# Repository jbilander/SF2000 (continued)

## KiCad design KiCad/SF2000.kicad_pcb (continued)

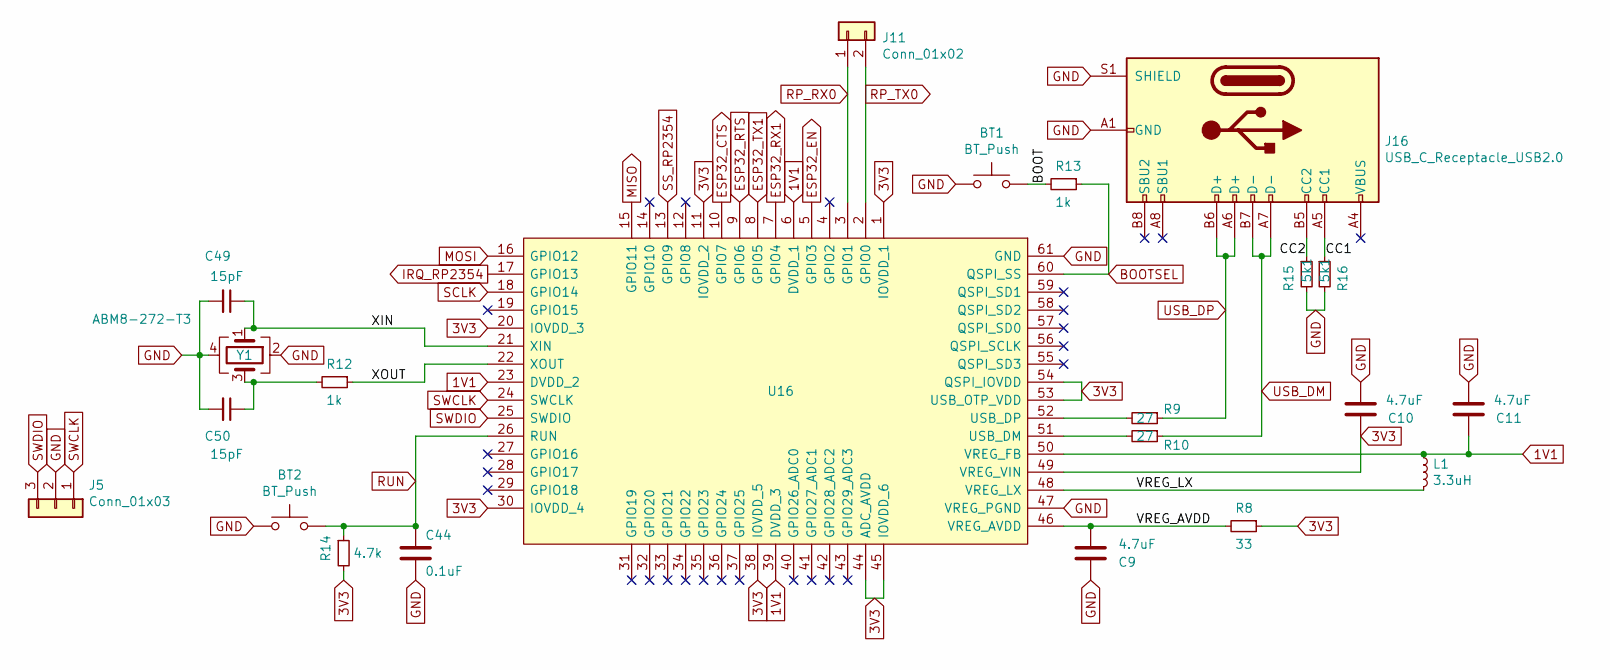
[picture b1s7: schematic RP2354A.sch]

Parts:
BT1, BT2: BT_Push; Sunrom_Tactile_Switch_3x4x2mm_SMD_2-Pin
C9, C10, C11: 4.7uF; C_1206_3216Metric_Pad1.33x1.80mm_HandSolder
C44: 0.1uF; C_0603_1608Metric_Pad1.08x0.95mm_HandSolder
C49, C50: 15pF; C_0603_1608Metric_Pad1.08x0.95mm_HandSolder
J5: Conn_01x03; PinHeader_1x03_P2.54mm_Vertical
J11: Conn_01x02; PinHeader_1x02_P2.54mm_Vertical
J16: USB_C_Receptacle_USB2.0; USB_C_Receptacle_HRO_TYPE-C-31-M-12
L1: 3.3uH; AOTAB201610S3R3101T
R8: 33; R_0603_1608Metric_Pad0.98x0.95mm_HandSolder
R9, R10: 27; R_0603_1608Metric_Pad0.98x0.95mm_HandSolder
R12, R13: 1k; R_0603_1608Metric_Pad0.98x0.95mm_HandSolder
R14: 4.7k; R_0603_1608Metric_Pad0.98x0.95mm_HandSolder
R15, R16: 5k1; R_0603_1608Metric_Pad0.98x0.95mm_HandSolder
U16: RP2354A; SC150913A4
Y1: ABM8-272-T3; Crystal_SMD_Abracon_ABM8G-4Pin_3.2x2.5mm

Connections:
1V1: C11.1, L1.1, U16.6 (DVDD_1), U16.23 (DVDD_2), U16.39 (DVDD_3), U16.50 (VREG_FB); also elsewhere on the board
3V3: C10.1, R8.1, R14.2, U16.1 (IOVDD_1), U16.11 (IOVDD_2), U16.20 (IOVDD_3), U16.30 (IOVDD_4), U16.38 (IOVDD_5), U16.44 (ADC_AVDD), U16.45 (IOVDD_6), U16.49 (VREG_VIN), U16.53 (USB_OTP_VDD), U16.54 (QSPI_IOVDD); also elsewhere on the board
/RP2354A/BOOT: BT1.2, R13.2
/RP2354A/CC1: J16.A5 (CC1), R16.1
/RP2354A/CC2: J16.B5 (CC2), R15.1
/RP2354A/VREG_AVDD: C9.1, R8.2, U16.46 (VREG_AVDD)
/RP2354A/VREG_LX: L1.2, U16.48 (VREG_LX)
/RP2354A/XIN: C49.1, U16.21 (XIN), Y1.1
/RP2354A/XOUT: R12.1, U16.22 (XOUT)
BOOTSEL: R13.1, U16.60 (QSPI_SS)
ESP32_CTS: U16.10 (GPIO7); also elsewhere on the board
ESP32_EN: U16.5 (GPIO3); also elsewhere on the board
ESP32_RTS: U16.9 (GPIO6); also elsewhere on the board
ESP32_RX1: U16.7 (GPIO4); also elsewhere on the board
ESP32_TX1: U16.8 (GPIO5); also elsewhere on the board
GND: BT1.1, BT2.1, C9.2, C10.2, C11.2, C44.2, C49.2, C50.2, J5.2, J16.A1 (GND), J16.A12 (GND), J16.B1 (GND), J16.B12 (GND), J16.S1 (SHIELD), R15.2, R16.2, U16.47 (VREG_PGND), U16.61 (GND), Y1.2, Y1.4; also elsewhere on the board
IRQ_RP2354: U16.17 (GPIO13); also elsewhere on the board
MISO: U16.15 (GPIO11); also elsewhere on the board
MOSI: U16.16 (GPIO12); also elsewhere on the board
unnamed: C50.1, R12.2, Y1.3
unnamed: J16.A4 (VBUS), J16.A9 (VBUS), J16.B4 (VBUS), J16.B9 (VBUS)
unnamed: R9.2, U16.52 (USB_DP)
unnamed: R10.2, U16.51 (USB_DM)
RP_RX0: J11.1, U16.3 (GPIO1)
RP_TX0: J11.2, U16.2 (GPIO0)
RUN: BT2.2, C44.1, R14.1, U16.26 (RUN)
SCLK: U16.18 (GPIO14); also elsewhere on the board
SS_RP2354: U16.13 (GPIO9); also elsewhere on the board
SWCLK: J5.1, U16.24 (SWCLK)
SWDIO: J5.3, U16.25 (SWDIO)
USB_DM: J16.A7 (D-), J16.B7 (D-), R10.1
USB_DP: J16.A6 (D+), J16.B6 (D+), R9.1

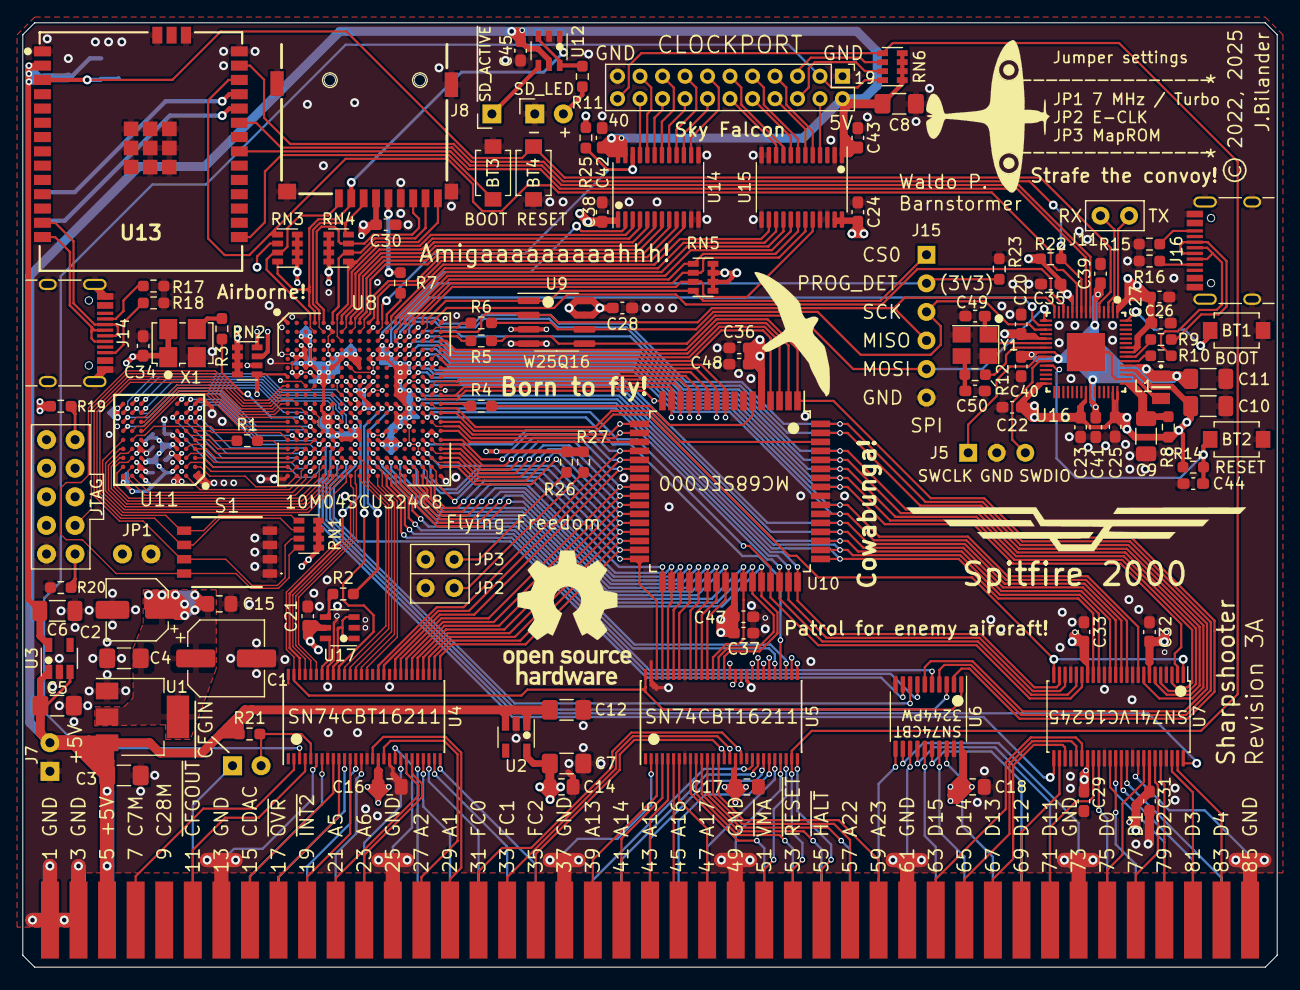
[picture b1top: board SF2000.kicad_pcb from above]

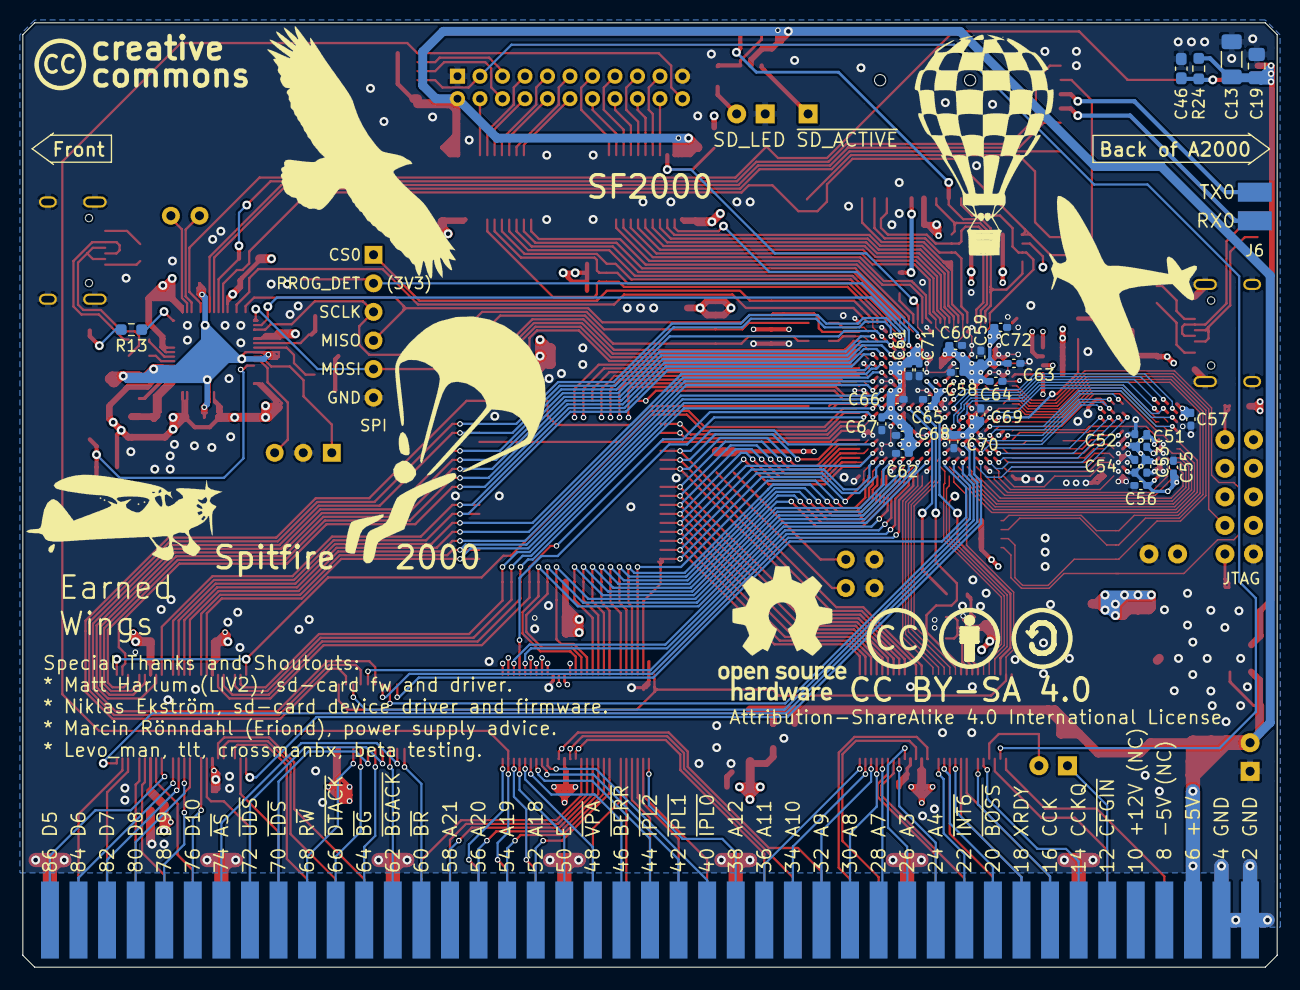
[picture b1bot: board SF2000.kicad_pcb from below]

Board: 4 copper layers, 111.5 x 83.9 mm, 146 parts (28 on the bottom side), 305 nets.

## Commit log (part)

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2021-12-31 added license
2022-01-01 added 86-pinout pdf
2022-01-05 added KiCAD files
2022-01-05 added Bus_Switch_Selection_Guide pdf
2022-01-06 fixed powering and layering, board and clearance settings etc
2022-01-07 added level shifters and routed all 5V-signals to them
2022-01-10 improved Power-circuits
2022-01-11 added Intel Max10 FPGA 10M04SCE144 symbol and footprint
2022-01-12 added 3D-model of intel MAX 10 FPGA 10M04SCE144
2022-01-12 modified EQFP-144 footprint central GND-pad to TH
2022-01-13 added Intel_MAX_10_Clocking_and_PLL_User_Guide.pdf
2022-01-13 added 68SEC000 symbol and footprint
2022-01-14 more dev, added nets
2022-01-16 added SRAM-chips to the design
2022-01-18 rotated SRAM footprints and routed a lot
2022-01-20 reconnected SRAMs and rerouted, and added a lot of caps
2022-01-21 added caps and did more routing
2022-01-22 routing and caps fixes
2022-01-23 more routing and caps fixes
2022-01-29 added Parallel_ATA_Interface_Reference_Design_Guide
2022-01-29 added Sheet for IDE_ROM_and_NOR-flash
2022-01-29 added Sheet for MicroSD
2022-01-31 added SDcard connector footprint
2022-01-31 added PLCC-32 custom smd footprint
2022-01-31 added IDE-pinheader with modified silkscreen
2022-01-31 added buffering for IDE, rearranged components a bit and did more routing
2022-02-01 added 3D-model of cay16-103j4lf
2022-02-01 added 3D-model of a PLCC-32 chip
2022-02-01 added 3D-model of MicroSD-slot
2022-02-01 deleted step-file
2022-02-01 added 3D-model of PLCC-32 socket
2022-02-01 added 3D-models to PCB
2022-02-03 modified PLCC-32 footprint and did some silkscreen fixes
2022-02-03 added MicroSD Card Socket document
2022-02-04 added pull-ups for SDIO and did some more routing
2022-02-08 more routing and pin assignments done to FPGA
2022-02-09 added Oscillator, pull-up resistor and more routing done
2022-02-10 more routing and fixing of FPGA pin assignments
2022-02-14 more routing, fixed JP6 placement and RN6 + some silkscreen fixes
2022-02-14 more routing done
2022-02-14 more routing and added two capacitors
2022-02-15 Fixed Switch and Jumper enumeration and silkscreen
2022-02-15 fixed JP6
2022-02-15 added ROM_WE signal/pin to FPGA, removed XRDY-signal/pin, and some silkscreen fixes
2022-02-15 added capacitor for FPGA VCC-pin 128
2022-02-15 added decoupling capacitor for Crystal Oscillator (X1), and some silkcreen fixes/labeling
2022-02-16 added R5,R6 pull-up/down resistors on IDE, added +5V-header for external powering during standalone programming FPGA
2022-02-28 added RC-debounce circuit for SW1
2022-03-01 added IDE Activity LED-header and a header for IDE-pin 39 /Active
2022-03-02 fixed labeling/enumeration of caps and resistors, and some silkscreen fixes
2022-03-02 added silhouette picture
2022-03-05 removed INT6_3V3 signal to FPGA and put in JP9 with a pull-up resistor instead
2022-03-09 added tables with Jumper-setting explanations on silkscreen
2022-03-21 deleted file
2022-03-21 Silkscreen fixes
2022-03-21 added pics
2022-04-07 small silkscreen fix marking +12V and -5V are NC (Not Connected)
2022-04-11 added symbol for GOWIN FPGA GW1N-UV9LQ144
2022-04-19 added footprint Pmod_Interface_Type_2A_SPI_PinSocket
2022-04-19 Re-routed for a GoWin FPGA GW1N-UV9LQ144 (or GW1N-UV4LQ144) and added a Pmod type 2A SPI-header.
2022-04-21 Fixed CLK-pin-assignments to use GCLKT-inputs, CDAC -> 11, C7M -> 23 and OSC_CLK -> 84
2022-06-22 changed FLASH_OE to pin 30 and AS_CPU_3V3 to pin 56 (GCLKT_5). Moved D11-D15 one step to the right (now pin 57-61).
2022-06-22 Removed RN5 and R10 (ROM_WE) pull-up resistors, using FPGA's built-in pull-ups instead.
2022-06-22 silkscreen fix
2022-07-03 Added resistor pack RN5 10k pull-ups for /WP, /AVEC, DONE, MODE
2022-07-04 Rev1A
2022-08-18 Separated BR_3V3, BG_3V3 --> BR_CPU_3V3, BG_CPU_3V3, BR_3V3, BG_3V3 (removed XRDY, INT6 and used those pins for BR_3V3, BG_3V3)
2022-08-20 made a custom QFP-64 footprint that fits 68SEC000 QFP-64 better
2022-08-20 changed to custom QFP-64 footprint for the 68SEC000
2022-08-20 changed to new custom made QFP-64 footprint for the 68SEC000 and re-routed
2022-08-20 added optional pull-up resistor for /ACTIVE signal
2022-08-21 Fixed 39LF040-footprint, elongated pads 0.2mm, easier to solder PLCC32-socket
2022-08-21 silkcreen fixes Revision 1B
2022-08-28 small mostly cosmetic fixes for final Revision 1B
2022-08-28 added rev1b schematic pdf
2022-12-04 added pic
2023-05-25 Updated schematic with correct U2 values
2025-04-01 Fixed symbol references for LM1117-3.3-Regulator and Oscillator_SG-8002CA, errors that occured when upgrading from KiCad 5.1.6 to 5.1.12
2025-04-01 Add symbol for Efinix Trion FPGA T8Q144C3
2025-04-01 Replace U8 with T8Q144C3 (Efinix Trion T8 FPGA)
2025-04-01 Assign 1.2V to VCC Core and VCCA_xx pins (PLL analog power supply pins)
2025-04-01 Assign 3.3V to all VCCIO-pins
2025-04-01 Assign E-CLK to GPIOL_25_CLK1 (pin 14)
2025-04-01 Assign JTAG pins
2025-04-02 Removed Pmod-header in order to make room for crystal oscillator and 1.2V voltage regulator.
2025-04-02 Placement of crystal oscillator
2025-04-02 Change R10 to 33 Ohm and used with crystal oscillator
2025-04-03 Removed JP2,JP3,JP4 and READY-signal, assigned JTAG-signals to 10k pull-up resistor array
2025-04-03 Adapted JTAG-header pin assignment to Efinix pinout standard
2025-04-03 Repurpose R1 to 100k pull-up resistor for CRESET_N
2025-04-03 Assign and route RESET_n line to CLK0
2025-04-03 more pin assignment and routing
2025-04-05 Renamed DONE to CDONE and routed track
2025-04-05 Fix JP1 and JP2, relocation of FC pins and placement of RN2 pull ups for JTAG, more routing etc
2025-04-05 pin assignment and routing of CFGIN_3V3, CFGOUT_3V3 and BR_3V3 signals
2025-04-06 Reassign C14 to 1.2V and place and route to it, fix of R2 placement and routing
2025-04-06 Routing 1.2V to input power pin 22 (FPGA) from C16, more fixes and routing around C16, rerouting of FC0,FC1 and a lot of other tracks
2025-04-06 More routing and placement of components to accomodate Efinix Trion T8 FPGA
2025-04-06 more pin assignment and routing to FPGA pin 65-72
2025-04-07 Removed WP# and FLASH_BUSY signals
2025-04-07 Assign FLASH_WE signal to FPGA pin 74 (GPIOR_158_TEST_N) and to 10k resistor array pin 1 in RN5
2025-04-07 Connect RST_3V3 to flash chip at U15
2025-04-07 swap position between AVEC and CDONE in resistor array RN5 and fix routing of those signals
2025-04-07 Routing of clock line from FPGA to CPU (CLKCPU-line)
2025-04-07 Route SPI_SS with a 10k pull-up resistor to JTAG-header
2025-04-07 Swap R1 and R2 references
2025-04-07 Fixed enumeration of single resistors references in ascending order
2025-04-07 Placement of capacitor for CRESET-signal and some more routing
2025-04-08 Update design with updated CPU QFP-64 footprint
2025-04-08 change U2 to ABLIC S-1132B43-M5T1U, change C6 value from 0.33uF to 0.47uF
2025-04-08 Add TLV74312PDBV 1.2V voltage regulator, change C7 value to 2.2uF
2025-04-08 Add SPI NOR Flash 8 Mbit in SOIC-8 package (AT25SF081B-SSH)
2025-04-08 Removed 3x2 jumper header J3, assigned JTAG header to now be J3 instead of JTAG1
2025-04-08 Remove IDE ACTIVE signal and its LED-driver IC (74LVC2G14)
2025-04-08 Fix placement and routing of components in 4V3 power supply area
2025-04-09 Route SD_LED signal to FPGA pin 75
2025-04-09 Remove IDE-header, add Clockport-header, fixed routing of AVEC and FLASH_OE signals and pull-ups
2025-04-09 Add INT6 signal, Move RN5 to SF2000_FPGA sheet
2025-04-10 Assign A16-A23 to FPGA and complete/route tracks
2025-04-10 Update clockport pinheader with pin numbering 19-40, remove unused footprint U18
2025-04-10 Preliminary positioning of buffers for clock port
2025-04-11 Adding RN6 pull-up resistor, Routing of A15-A6 to FPGA and more cleanup
2025-04-11 clockport rework
2025-04-12 Add silkscreen art
2025-04-12 Route A2-A5 to clockport
2025-04-13 Add symbol for 74AHCT3G14
2025-04-13 Replace 74LVC245A with 74AHCT3G14 for clockport control signals
2025-04-14 Add SD_LED & LED Activity circuit and small fixes and routing around the clockport area
2025-04-14 More routing and cleanup of old traces, removed old Gowin FPGA symbol and footprint
2025-04-15 Fixed routing D0-D7 lines plus some cleanup and routing of power supply to FPGA power pins
2025-04-15 Fixed driver bank select jumper for ROM at U14, pulled-up by vacant resistor in RN3
2025-04-15 Swap position of BOSS and INT2 signal in FPGA and level shifters
2025-04-15 Remove INT6_3V3 signal and relocate JP2 to use this pin instead
2025-04-15 Remove INT2_3V3 pin and instead use it for JP3
2025-04-15 Add caps for 1.2V voltage regulator and place and route the area
2025-04-16 Placement of C39
2025-04-16 Route C37 decoupling power supply to pin 12 FPGA
2025-04-16 Placement of C23 decoupling cap and routing of 1.2V supply to pin 13
2025-04-17 Routing 3.3V power via C45 bypass cap to FPGA pin 122
2025-04-17 Remove R12,R13
2025-04-17 Routing of 3.3V supply to SD-slot Power pin via decoupling cap C43
2025-04-17 Change LED-circuit to active low and controlled by SD-cards CS-signal
2025-04-18 Fix of SD-card control signals and routing
2025-04-18 Add symnbol for 74AHCT14PW
2025-04-18 Replace 74AHCT3G14 with a hex inverter 74AHCT14PW and also simplify and drive the LED circuit from this latter IC.
2025-04-18 Add decoupling cap and route 1.2V power to input pin 73 on FPGA
2025-04-18 Add decoupling caps and route 3.3V power to input pin 88,91,95 on FPGA
2025-04-19 Add decoupling cap and route 1.2V power to input pin 85 and 96 on FPGA
2025-04-19 Swap references for resistors R8 and R10
2025-04-19 Remove resistors R9,R10,R11 not being used any longer
2025-04-19 Fixed power routing of 1.2V and 3.3V supply to FPGA pins 85,88,91,95 and 96, some re-routing was required
2025-04-19 Routing of star power on inner layer for 1.2V supply to all 1.2V power input pins on FPGA
2025-04-20 Fixed references to capacitors in ascending order by size and value
2025-04-20 Fix continuous enumeration for voltage regulators and integrated circuits (U1 to U17)
2025-04-20 Fix continuous enumeration for pin-headers (J1 to J12)
2025-04-20 Small GND fix improvement
2025-04-20 Change hole size on SD-card footprint from 1.2 mm to 1 mm to better hold and align slot during assembly
2025-04-20 silkscreen fix orientation labels on the backside
2025-04-21 Updated Spitfire silkscreen footprint
2025-04-21 Add creative commons symbol and text
2025-04-21 Add silkscreen art to backside
2025-04-22 Add CC BY-SA footprint symbols
2025-04-22 Add license information CC BY-SA 4.0 on backside silkscreen
2025-04-22 Add silkscreen art footprints
2025-04-22 Add more silkscreen art on backside
2025-04-23 Add SN74LVC2G86DCUR symbol
2025-04-23 Replaced U7 (SN74AUP1T87DCKR) with a dual XOR gate (SN74LVC2G86DCUR) and generate 14 MHz by also routing CDAC here
2025-05-06 Change U9 (SPI NOR Flash) value from AT25SF081B-SSH to W25Q128JVSIQ
2025-05-06 Swap pin assignment for FLASH_OE (pin 72) with ROM_WE (pin 32)
2025-05-08 Relocated ROM_OE to pin 80, SD_MISO to pin 81 and SD_CD to 82 to better prepare for 4-bit SDIO should ROM-chip U13 be removed
2025-05-08 Updated board setting minimum via drill 0.5/0.3 mm and SolderMaskClearance=0
2025-05-09 Change U9 value from W25Q128JVSIQ to AT25SF161B-SSHD-T
2025-05-25 Silkscreen fix, spelling of Airborne
2025-07-21 Breakout of JP1 to its own header, removing it from JTAG-header
2025-07-21 Update the spi flash rom (U9) to W25Q16JVSNIQ
2025-07-21 Change to 7M clock input instead of C14M from XOR-chip U7, removed CDAC
2025-07-22 Replace /OVR with /INT2 signal
2025-07-22 Replace CDAC with /INT6 signal
2025-07-24 Add SDRAM W9812G6KH-6 to library
2025-07-24 Reconnect U8 pin 123 from INT6_3V3 to WE_BANK1_EVEN, Reconnect U8 pin 72 from ROM_WE to INT6_3V3
2025-07-25 Add back SRAM footprints on underside U16,U17
2025-07-26 Change references: C11 to C10, C10 to C9, C9 to C8, C8 to C7, change C11 from value 10uF to 0.1uF, change C11 to size 0805 footprint
2025-07-29 Put SCLK, MISO and MOSI in 2x5 pin-header second row
2025-07-29 Change R4 value from 330 to 220
